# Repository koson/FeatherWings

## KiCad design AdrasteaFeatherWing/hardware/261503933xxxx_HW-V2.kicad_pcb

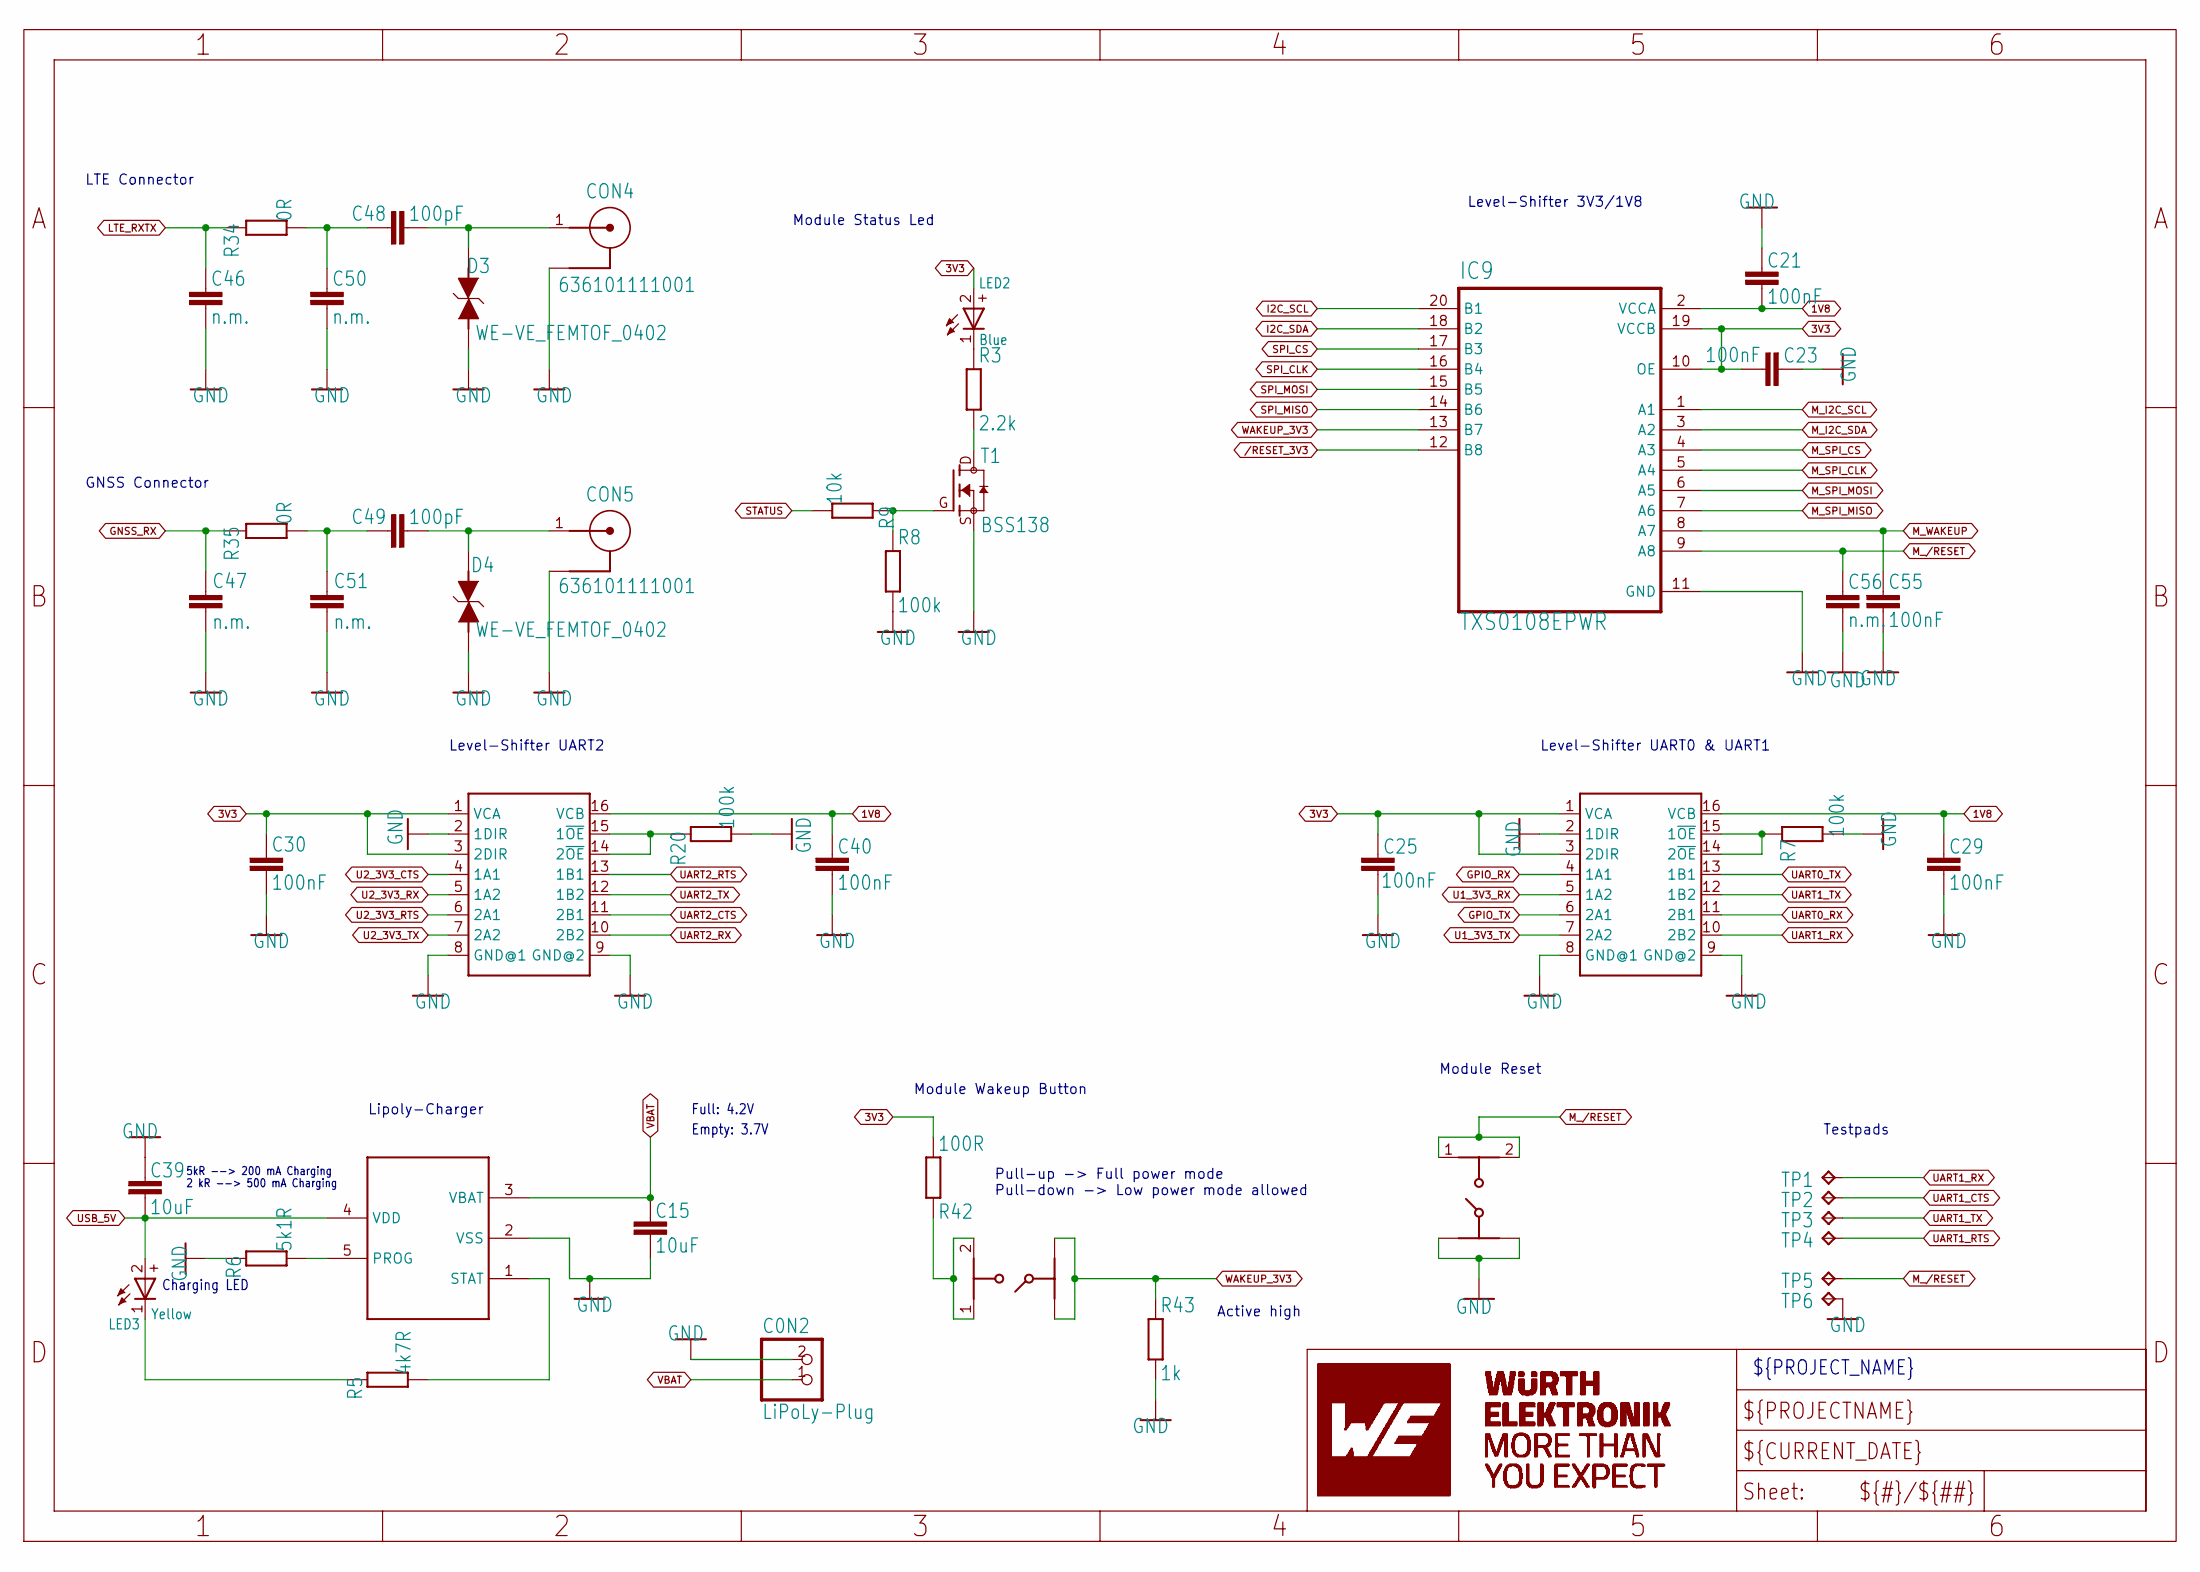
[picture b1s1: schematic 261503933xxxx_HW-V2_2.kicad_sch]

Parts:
C0N2: LiPoLy-Plug; JST-PH-2-SMT-RA-ADRASTEA-ANGEPASST
C15: 10uF; C0402_IPC
C21, C23, C25, C29, C30, C40, C55: 100nF; C0402_IPC
C39: 10uF; C0603_IPC
C46, C47, C50, C51, C56: n.m.; C0402_IPC
C48, C49: 100pF; C0402_IPC
CON4, CON5: 636101111001
D3, D4: WE-VE_FEMTOF_0402
IC5, IC8: SN74AVC4T245PWR; PW16(TSSOP16)
IC7: MCP73831T-2ACI/OT; SOT23-5
IC9: TXS0108EPWR; SOP65P640X120-20N
LED2: Blue; WL-SMSW_1204_A
LED3: Yellow; WL-SMSW_1204_A
R3: 2.2k; R0402_IPC
R5: 4k7R; R0402_IPC
R6: 5k1R; R0402_IPC
R7, R8, R20: 100k; R0402_IPC
R9: 10k; R0402_IPC
R34, R35: 0R; R0402_IPC
R42: 100R; R0402_IPC
R43: 1k; R0402_IPC
S1, S2: 434331013822
T1: BSS138
TP1, TP2, TP3, TP4, TP5, TP6: TP15R

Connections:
1V8: C21.1, C29.2, C40.2, IC5.16 (VCB), IC8.16 (VCB), IC9.2 (VCCA); also elsewhere on the board
3V3: C23.1, C25.2, C30.2, IC5.1 (VCA), IC5.3 (2DIR), IC8.1 (VCA), IC8.3 (2DIR), IC9.10 (OE), IC9.19 (VCCB), LED2.2 (+), R42.1; also elsewhere on the board
/RESET_3V3: IC9.12 (B8); also elsewhere on the board
GND: C0N2.2 (1), C15.2, C21.2, C23.2, C25.1, C29.1, C30.1, C39.1, C40.1, C46.1, C47.1, C50.1, C51.1, C55.1, C56.1, CON4.2, CON4.3 (2), CON5.2, CON5.3 (2), D3.2, D4.2, IC5.2 (1DIR), IC5.8 (GND@1), IC5.9 (GND@2), IC7.2 (VSS), IC8.2 (1DIR), IC8.8 (GND@1), IC8.9 (GND@2), IC9.11 (GND), R6.1, R7.2, R8.2, R20.2, R43.2, S1.3, S1.4, S1.5 (3), S1.6 (4), T1.S, TP6.P$1; also elsewhere on the board
GNSS_RX: C47.2, R35.2; also elsewhere on the board
GPIO_RX: IC5.4 (1A1); also elsewhere on the board
GPIO_TX: IC5.6 (2A1); also elsewhere on the board
I2C_SCL: IC9.20 (B1); also elsewhere on the board
I2C_SDA: IC9.18 (B2); also elsewhere on the board
LS_ISO_CTRL1: IC8.14 (2~OE), IC8.15 (1~OE), R20.1
LTE_RXTX: C46.2, R34.2; also elsewhere on the board
M_/RESET: C56.2, IC9.9 (A8), S1.1, S1.2, TP5.P$1; also elsewhere on the board
M_I2C_SCL: IC9.1 (A1); also elsewhere on the board
M_I2C_SDA: IC9.3 (A2); also elsewhere on the board
M_SPI_CLK: IC9.5 (A4); also elsewhere on the board
M_SPI_CS: IC9.4 (A3); also elsewhere on the board
M_SPI_MISO: IC9.7 (A6); also elsewhere on the board
M_SPI_MOSI: IC9.6 (A5); also elsewhere on the board
M_WAKEUP: C55.2, IC9.8 (A7); also elsewhere on the board
unnamed: LED2.1 (-), R3.1
unnamed: C49.1, CON5.1, D4.1
unnamed: C48.1, CON4.1, D3.1
unnamed: R42.2, S2.1, S2.2
unnamed: C48.2, C50.2, R34.1
unnamed: R3.2, T1.D
unnamed: C49.2, C51.2, R35.1
unnamed: R8.1, R9.2, T1.G
unnamed: LED3.1 (-), R5.1
unnamed: IC7.5 (PROG), R6.2
unnamed: IC5.14 (2~OE), IC5.15 (1~OE), R7.1
SPI_CLK: IC9.16 (B4); also elsewhere on the board
SPI_CS: IC9.17 (B3); also elsewhere on the board
SPI_MISO: IC9.14 (B6); also elsewhere on the board
SPI_MOSI: IC9.15 (B5); also elsewhere on the board
STAT: IC7.1 (STAT), R5.2
STATUS: R9.1; also elsewhere on the board
U1_3V3_RX: IC5.5 (1A2); also elsewhere on the board
U1_3V3_TX: IC5.7 (2A2); also elsewhere on the board
U2_3V3_CTS: IC8.4 (1A1); also elsewhere on the board
U2_3V3_RTS: IC8.6 (2A1); also elsewhere on the board
U2_3V3_RX: IC8.5 (1A2); also elsewhere on the board
U2_3V3_TX: IC8.7 (2A2); also elsewhere on the board
UART0_RX: IC5.11 (2B1); also elsewhere on the board
UART0_TX: IC5.13 (1B1); also elsewhere on the board
UART1_CTS: TP2.P$1; also elsewhere on the board
UART1_RTS: TP4.P$1; also elsewhere on the board
UART1_RX: IC5.10 (2B2), TP1.P$1; also elsewhere on the board
UART1_TX: IC5.12 (1B2), TP3.P$1; also elsewhere on the board
UART2_CTS: IC8.11 (2B1); also elsewhere on the board
UART2_RTS: IC8.13 (1B1); also elsewhere on the board
UART2_RX: IC8.10 (2B2); also elsewhere on the board
UART2_TX: IC8.12 (1B2); also elsewhere on the board
USB_5V: C39.2, IC7.4 (VDD), LED3.2 (+); also elsewhere on the board
VBAT: C0N2.1 (2), C15.1, IC7.3 (VBAT); also elsewhere on the board
WAKEUP_3V3: IC9.13 (B7), R43.1, S2.3, S2.4, S2.5 (3), S2.6 (4); also elsewhere on the board

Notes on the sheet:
Charging LED
Module Reset
Module Wakeup Button
Level-Shifter 3V3/1V8
Level-Shifter UART2
LTE Connector
${PROJECT_NAME}
Pull-up -> Full power mode Pull-down -> Low power mode allowed
5kR --> 200 mA Charging
Module Status Led
Lipoly-Charger
Full: 4.2V
Empty: 3.7V
Level-Shifter UART0 & UART1
GNSS Connector
2 kR --> 500 mA Charging
Testpads
Active high

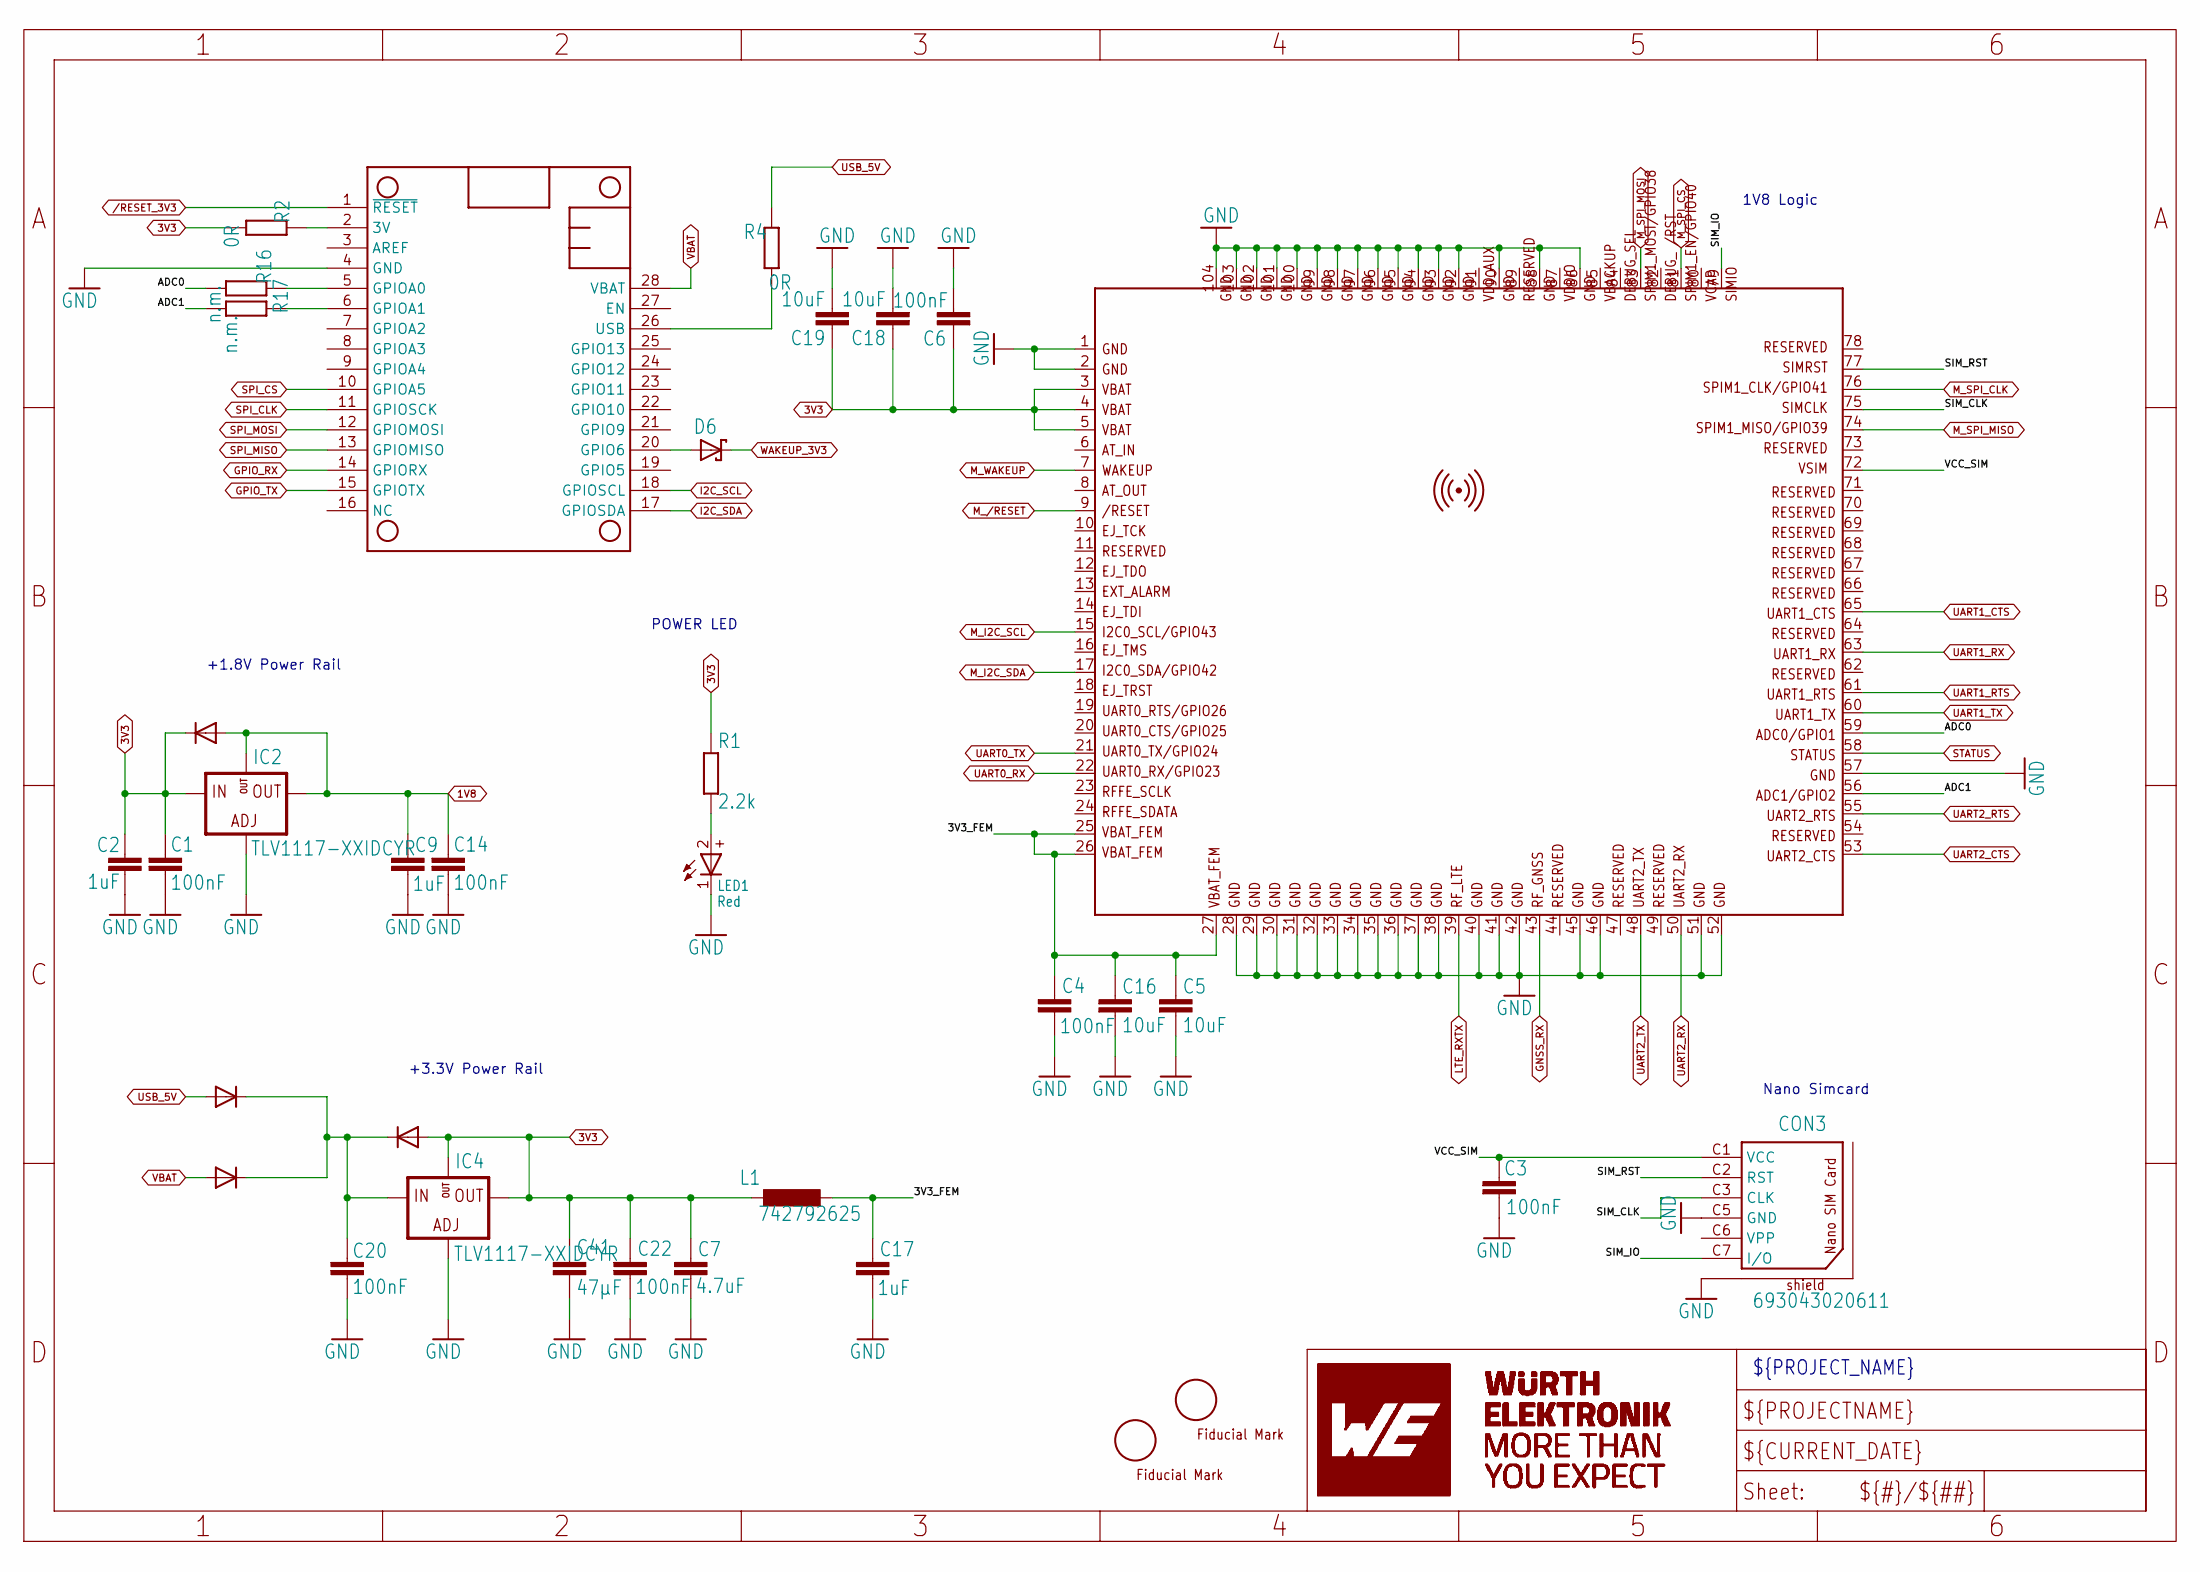
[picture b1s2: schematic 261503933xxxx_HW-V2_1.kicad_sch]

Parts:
C1, C3, C4, C6, C14, C20, C22: 100nF; C0402_IPC
C2, C9, C17: 1uF; C0402_IPC
C5, C16, C18, C19: 10uF; C0402_IPC
C7: 4.7uF; C0402_IPC
C41: 47µF; C0805
CON3: 693043020611
D1, D2: BAS16; SOT23@1
D6: BAT540402_X1-DFN1006-2; X1-DFN1006-2
D7, D8: DFLS130L-7; SOD123_POWERDI
IC1: WIRL-CELL-2615011136000
IC2, IC4: TLV1117-XXIDCYR; SOT223-4
L1: 742792625; L0603_WE-MK
LED1: Red; WL-SMSW_1204_A
MS1: FEATHERWING_80MM
O1, O2: OPT_MARKE05; OPT_M_05
R1: 2.2k; R0402_IPC
R2, R4: 0R; R0603_IPC
R16, R17: n.m.; R0402_IPC

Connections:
1V8: C9.1, C14.2, D1.1 (A), IC2.2 (OUT), IC2.4 (OUT@2); also elsewhere on the board
3V: MS1.2 (3V), R2.2
3V3: C1.2, C2.1, C6.2, C7.1, C18.1, C19.1, C22.2, C41.P$1 (1), D1.3 (C), D2.1 (A), IC1.3 (VBAT@1), IC1.4 (VBAT@2), IC1.5 (VBAT@3), IC2.3 (IN), IC4.2 (OUT), IC4.4 (OUT@2), L1.1, R1.2, R2.1; also elsewhere on the board
3V3_FEM: C4.2, C5.1, C16.1, C17.1, IC1.25 (VBAT_FEM@1), IC1.26 (VBAT_FEM@2), IC1.27 (VBAT_FEM@3), L1.2
5V_IN: C20.2, D2.3 (C), D7.K (C), D8.K (C), IC4.3 (IN)
/RESET_3V3: MS1.1 (~RESET); also elsewhere on the board
ADC0: IC1.59 (ADC0/GPIO1), R16.1
ADC1: IC1.56 (ADC1/GPIO2), R17.1
ADC_0: MS1.5 (GPIOA0), R16.2
ADC_1: MS1.6 (GPIOA1), R17.2
FEATHER_USB: MS1.26 (USB), R4.1
GND: C1.1, C2.2, C3.2, C4.1, C5.2, C6.1, C7.2, C9.2, C14.1, C16.2, C17.2, C18.2, C19.2, C20.1, C22.1, C41.P$2 (2), CON3.C5 (GND), CON3.S1 (SHIELD), CON3.S2 (SHIELD), CON3.S3 (SHIELD), CON3.S4 (SHIELD), CON3.S5 (SHIELD), CON3.S6 (SHIELD), IC1.1 (GND@1), IC1.2 (GND@2), IC1.28 (GND@3), IC1.29 (GND@4), IC1.30 (GND@5), IC1.31 (GND@6), IC1.32 (GND@7), IC1.33 (GND@8), IC1.34 (GND@9), IC1.35 (GND@10), IC1.36 (GND@11), IC1.37 (GND@12), IC1.38 (GND@13), IC1.40 (GND@14), IC1.41 (GND@15), IC1.42 (GND@16), IC1.45 (GND@17), IC1.46 (GND@18), IC1.51 (GND@19), IC1.52 (GND@20), IC1.57 (GND@21), IC1.86 (GND@22), IC1.88 (GND@23), IC1.90 (GND@24), IC1.92 (GND@25), IC1.93 (GND@26), IC1.94 (GND@27), IC1.95 (GND@28), IC1.96 (GND@29), IC1.97 (GND@30), IC1.98 (GND@31), IC1.99 (GND@32), IC1.100 (GND@33), IC1.101 (GND@34), IC1.102 (GND@35), IC1.103 (GND@36), IC1.104 (GND@37), IC2.1 (ADJ), IC4.1 (ADJ), LED1.1 (-), MS1.4 (GND); also elsewhere on the board
GNSS_RX: IC1.43 (RF_GNSS_ANT); also elsewhere on the board
GPIO_RX: MS1.14 (GPIORX); also elsewhere on the board
GPIO_TX: MS1.15 (GPIOTX); also elsewhere on the board
I2C_SCL: MS1.18 (GPIOSCL); also elsewhere on the board
I2C_SDA: MS1.17 (GPIOSDA); also elsewhere on the board
LTE_RXTX: IC1.39 (RF_RXTX); also elsewhere on the board
M_/RESET: IC1.9 (/RESET); also elsewhere on the board
M_I2C_SCL: IC1.15 (I2C0_SCL/GPIO43); also elsewhere on the board
M_I2C_SDA: IC1.17 (I2C0_SDA/GPIO42); also elsewhere on the board
M_SPI_CLK: IC1.76 (SPIM1_CLK/GPIO41); also elsewhere on the board
M_SPI_CS: IC1.81 (SPIM1_EN/GPIO40); also elsewhere on the board
M_SPI_MISO: IC1.74 (SPIM1_MISO/GPIO39); also elsewhere on the board
M_SPI_MOSI: IC1.83 (SPIM1_MOSI/GPIO38); also elsewhere on the board
M_WAKEUP: IC1.7 (WAKEUP); also elsewhere on the board
unnamed: LED1.2 (+), R1.1
unnamed: D6.2 (A), MS1.20 (GPIO6)
SIM_CLK: CON3.C3 (CLK), IC1.75 (SIMCLK)
SIM_IO: CON3.C7 (I/O), IC1.79 (SIMIO)
SIM_RST: CON3.C2 (RST), IC1.77 (SIMRST)
SPI_CLK: MS1.11 (GPIOSCK); also elsewhere on the board
SPI_CS: MS1.10 (GPIOA5); also elsewhere on the board
SPI_MISO: MS1.13 (GPIOMISO); also elsewhere on the board
SPI_MOSI: MS1.12 (GPIOMOSI); also elsewhere on the board
STATUS: IC1.58 (STATUS); also elsewhere on the board
UART0_RX: IC1.22 (UART0_RX/GPIO23); also elsewhere on the board
UART0_TX: IC1.21 (UART0_TX/GPIO24); also elsewhere on the board
UART1_CTS: IC1.65 (UART1_CTS); also elsewhere on the board
UART1_RTS: IC1.61 (UART1_RTS); also elsewhere on the board
UART1_RX: IC1.63 (UART1_RX); also elsewhere on the board
UART1_TX: IC1.60 (UART1_TX); also elsewhere on the board
UART2_CTS: IC1.53 (UART2_CTS); also elsewhere on the board
UART2_RTS: IC1.55 (UART2_RTS); also elsewhere on the board
UART2_RX: IC1.50 (UART2_RX); also elsewhere on the board
UART2_TX: IC1.48 (UART2_TX); also elsewhere on the board
USB_5V: D7.A, R4.2; also elsewhere on the board
VBAT: D8.A, MS1.28 (VBAT); also elsewhere on the board
VCC_SIM: C3.1, CON3.C1 (VCC), IC1.72 (VSIM)
WAKEUP_3V3: D6.1 (C); also elsewhere on the board

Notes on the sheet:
+1.8V Power Rail
${PROJECT_NAME}
1V8 Logic
+3.3V Power Rail
POWER LED
Nano Simcard

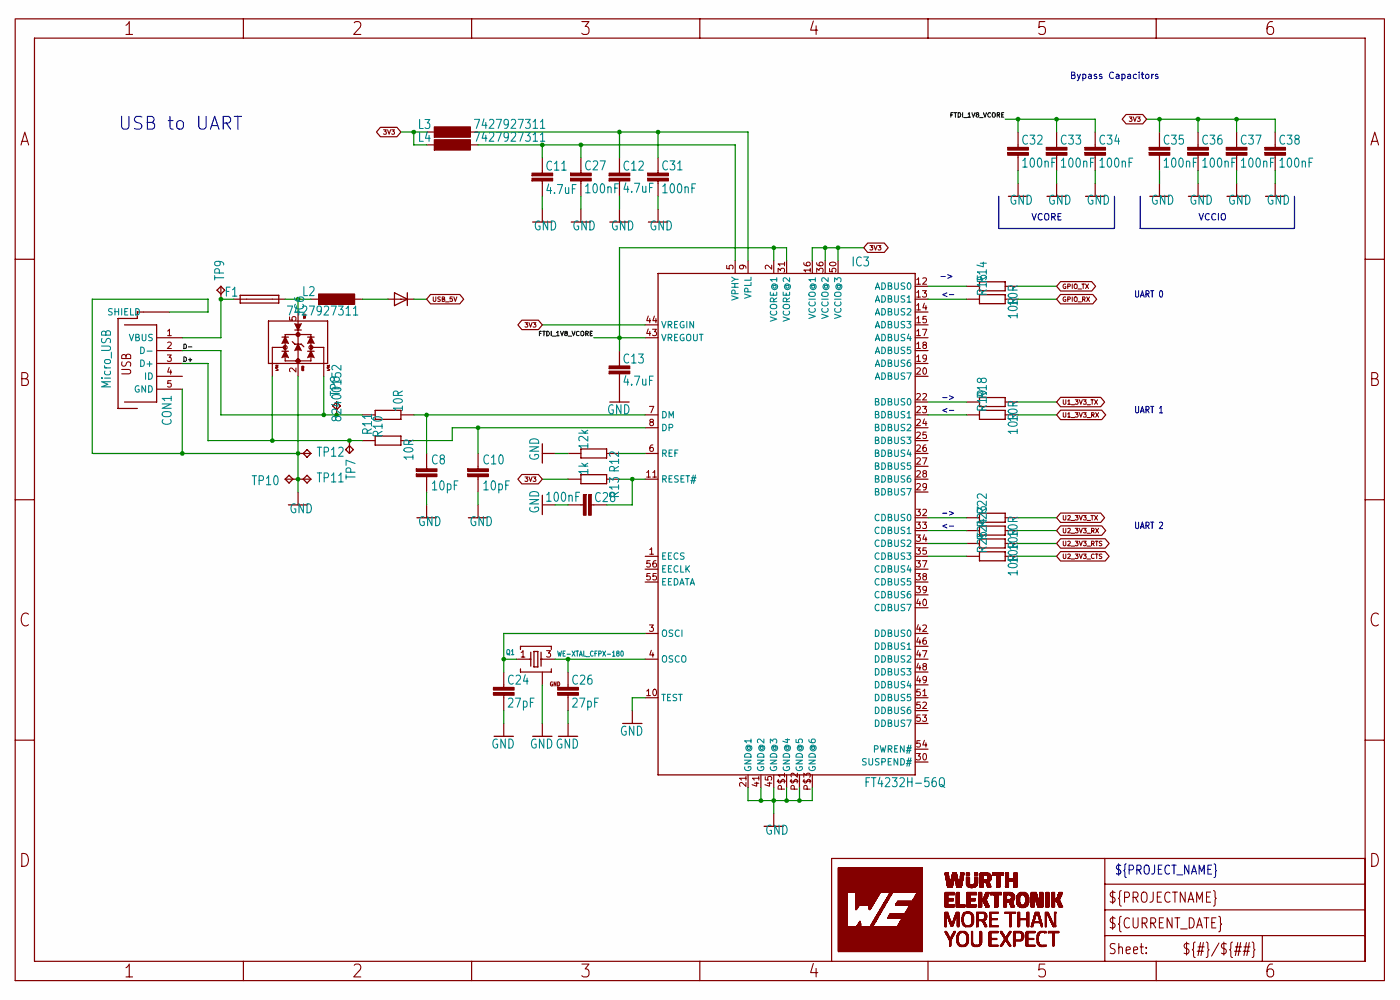
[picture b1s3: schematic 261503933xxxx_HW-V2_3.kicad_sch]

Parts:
C8, C10: 10pF; C0402_IPC
C11, C12, C13: 4.7uF; C0402_IPC
C24, C26: 27pF; C0402_IPC
C27, C28, C31, C32, C33, C34, C35, C36, C37, C38: 100nF; C0402_IPC
CON1: Micro_USB; 629105150521
D5: DFLS130L-7; SOD123_POWERDI
F1: ERB-RD1R50X; 0402
IC3: FT4232H-56Q; VQFN-56
IC6: 82400152; WE-TVS_SOT563
L2, L3, L4: 7427927311; L0402_WE-MK
Q1: WE-XTAL_CFPX-180
R10, R11, R14, R15, R18, R19, R22, R23, R24, R25: 10R; R0402_IPC
R12: 12k; R0402_IPC
R13: 1k; R0402_IPC
TP7, TP8, TP9, TP10, TP11, TP12: TP15R

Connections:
3V3: C35.2, C36.2, C37.2, C38.2, IC3.16 (VCCIO@1), IC3.36 (VCCIO@2), IC3.44 (VREGIN), IC3.50 (VCCIO@3), L3.P$2 (2), L4.P$2 (2), R13.1; also elsewhere on the board
D+: CON1.3 (D+), IC6.3 (I/O2), IC6.4 (I/O2), R10.1, TP7.P$1
D-: CON1.2 (D-), IC6.1 (I/O1), IC6.6 (I/O1), R11.2, TP8.P$1
FTDI_1V8_VCORE: C13.1, C32.2, C33.2, C34.2, IC3.2 (VCORE@1), IC3.31 (VCORE@2), IC3.43 (VREGOUT)
FTDI_CTS#_CH-C: IC3.35 (CDBUS3), R25.1
FTDI_RESET: C28.2, IC3.11 (RESET#), R13.2
FTDI_RTS#_CH-C: IC3.34 (CDBUS2), R24.1
FTDI_RXD_CH-A: IC3.13 (ADBUS1), R15.1
FTDI_RXD_CH-B: IC3.23 (BDBUS1), R19.1
FTDI_RXD_CH-C: IC3.33 (CDBUS1), R23.1
FTDI_TXD_CH-A: IC3.12 (ADBUS0), R14.1
FTDI_TXD_CH-B: IC3.22 (BDBUS0), R18.1
FTDI_TXD_CH-C: IC3.32 (CDBUS0), R22.1
GND: C8.1, C10.1, C11.2, C12.2, C13.2, C24.1, C26.1, C27.1, C28.1, C31.1, C32.1, C33.1, C34.1, C35.1, C36.1, C37.1, C38.1, CON1.5 (GND), CON1.SHELL (SHIELD), CON1.SHELL1 (SHIELD), CON1.SHELL2 (SHIELD), CON1.SHELL3 (SHIELD), IC3.10 (TEST), IC3.21 (GND@1), IC3.41 (GND@2), IC3.45 (GND@3), IC3.P$1 (GND@4), IC3.P$2 (GND@5), IC3.P$3 (GND@6), IC6.2 (GND), Q1.2 (GND), Q1.4 (GND), R12.1, TP10.P$1, TP11.P$1, TP12.P$1; also elsewhere on the board
GPIO_RX: R15.2; also elsewhere on the board
GPIO_TX: R14.2; also elsewhere on the board
unnamed: C8.2, IC3.7 (DM), R11.1
unnamed: C10.2, IC3.8 (DP), R10.2
unnamed: D5.A, L2.P$1 (1)
unnamed: F1.2, IC6.5 (VDD), L2.P$2 (2)
unnamed: C11.1, C27.2, IC3.5 (VPHY), L4.P$1 (1)
unnamed: C12.1, C31.2, IC3.9 (VPLL), L3.P$1 (1)
unnamed: IC3.6 (REF), R12.2
unnamed: C24.2, IC3.3 (OSCI), Q1.1
unnamed: C26.2, IC3.4 (OSCO), Q1.3 (2)
U1_3V3_RX: R19.2; also elsewhere on the board
U1_3V3_TX: R18.2; also elsewhere on the board
U2_3V3_CTS: R25.2; also elsewhere on the board
U2_3V3_RTS: R24.2; also elsewhere on the board
U2_3V3_RX: R23.2; also elsewhere on the board
U2_3V3_TX: R22.2; also elsewhere on the board
USB_5V: D5.K (C); also elsewhere on the board
VBUS: CON1.1 (VBUS), F1.1, TP9.P$1

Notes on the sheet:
UART 1
${PROJECT_NAME}
VCCIO
USB to UART
UART 2
VCORE
Bypass Capacitors
UART 0

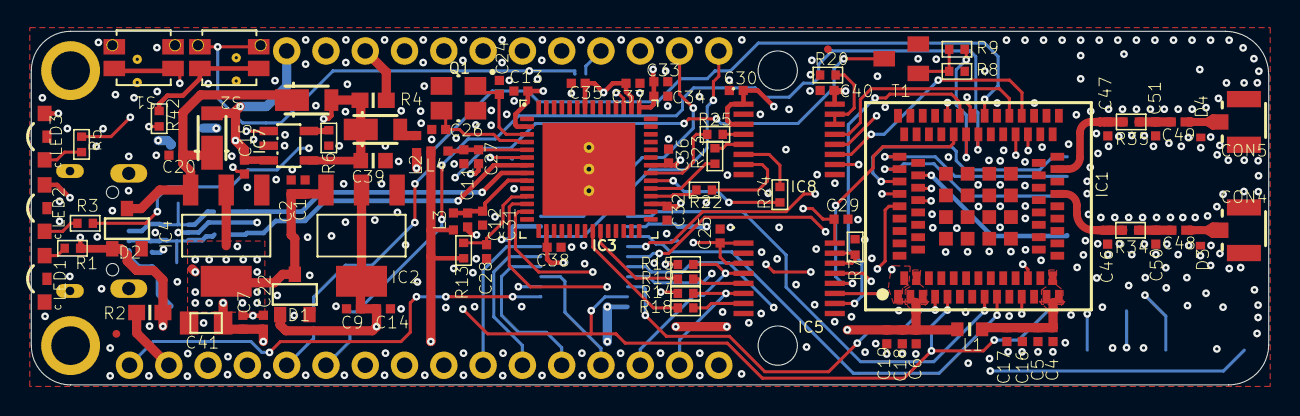
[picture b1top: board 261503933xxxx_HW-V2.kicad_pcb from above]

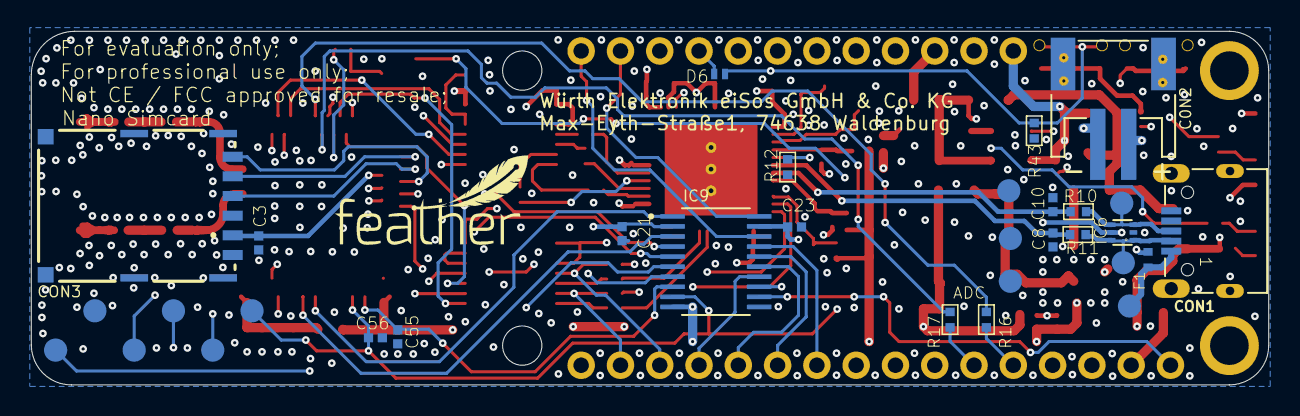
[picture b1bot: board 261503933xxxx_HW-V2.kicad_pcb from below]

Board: 4 copper layers, 80.0 x 22.9 mm, 127 parts (33 on the bottom side), 91 nets.

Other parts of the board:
U$4: FEATHER_12MM

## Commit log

2024-04-05 import to kicad
2024-04-05 export kicad libs
